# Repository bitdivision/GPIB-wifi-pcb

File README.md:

# GPIB-wifi-pcb
**NOTE**: This is currently not working.
A GPIB adapter using an ESP8266 for wifi functionality and a Cortex M0.

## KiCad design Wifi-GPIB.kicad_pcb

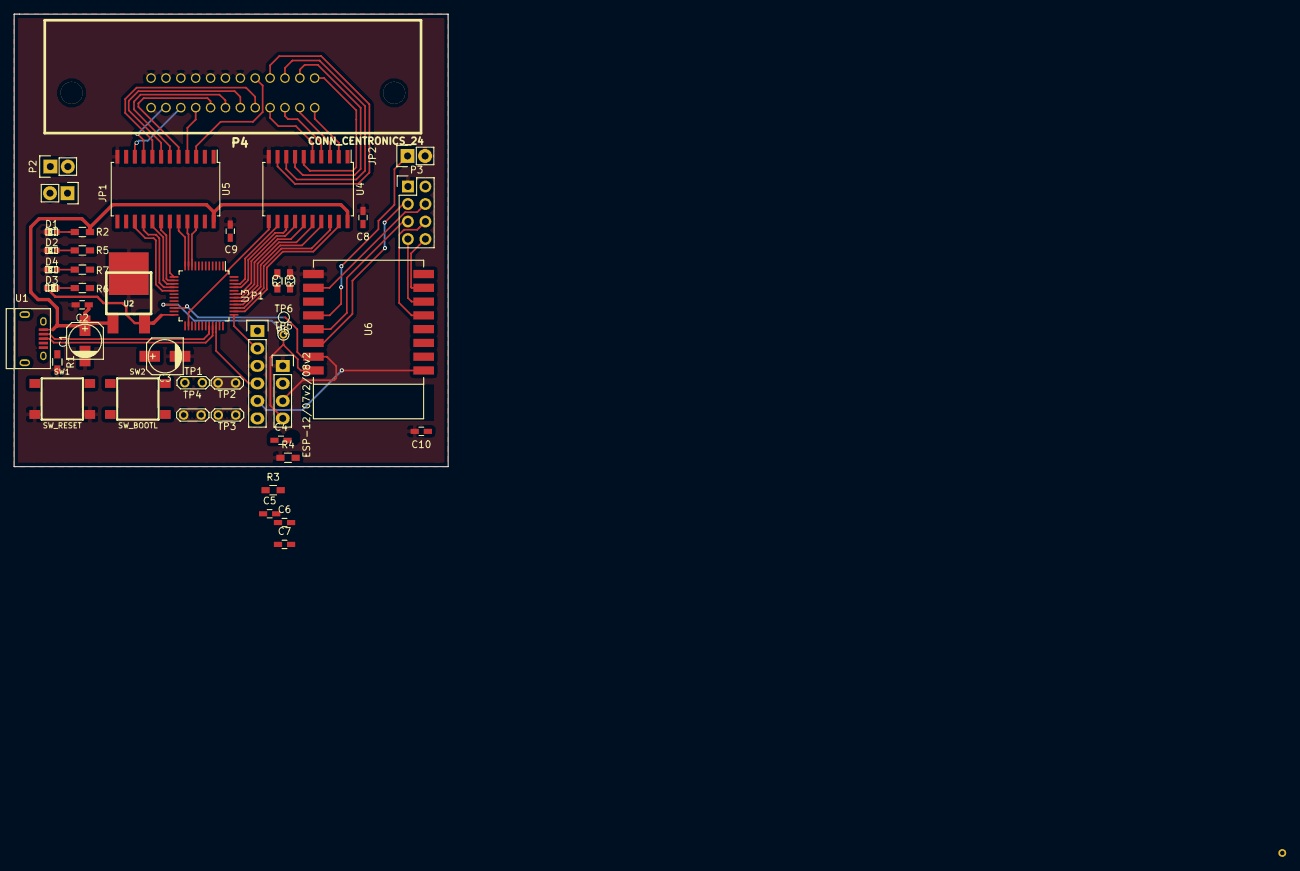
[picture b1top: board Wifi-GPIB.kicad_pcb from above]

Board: 2 copper layers, 63.0 x 65.7 mm, 44 parts (0 on the bottom side), 66 nets.

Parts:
C1, C3: 47u; c_elec_5x5.3
C2: 0.33u; C_0603_HandSoldering
C4, C5, C6, C8, C9: 100n; C_0603_HandSoldering
C7: 1u; C_0603_HandSoldering
C10: C; C_0603_HandSoldering
D1: PWR; LED-0603
D2: WIFI; LED-0603
D3: USB; LED-0603
D4: GPIB; LED-0603
JP1: USB_LED; Pin_Header_Straight_1x02
JP2: ESP_FLASH_JUMP; Pin_Header_Straight_1x02
P1: SWD; Pin_Header_Straight_1x06
P2: USART; Pin_Header_Straight_1x02
P3: ESP_EXPANSION; Pin_Header_Straight_2x04
P4: CONN_CENTRONICS_24; gpib_conn_male
P5: ESP_PROG; Pin_Header_Straight_1x04
R1: 100k; R_0603_HandSoldering
R2: 270; R_0603_HandSoldering
R3, R4, R5, R6, R7, R8, R9: R; R_0603_HandSoldering
SW1: SW_RESET; SW_PUSH_SMD
SW2: SW_BOOTL; SW_PUSH_SMD
TP1, TP2, TP3, TP4: TESTPOINT
TP5, TP6: TESTPOINT; PINTST
U1: MICRO-B_USB; USB_Micro-B
U2: BA33BC0FP-E2; TO-252
U3: STM32F072CBT6; LQFP-48_7x7mm_Pitch0.5mm
U4: SN75160B; SOIC-20_7.5x12.8mm_Pitch1.27mm
U5: SN75162B; SOIC-24_7.5x15.4mm_Pitch1.27mm
U6: ESP-12/07v2/08v2; ESP-07

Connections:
+3.3V: C3.1, C4.2, C6.2, C7.2, C10.1, D3.1, P1.1, P3.2, P5.2, R3.2, R8.1, SW2.2, TP1.1, U2.3, U3.9, U3.24, U3.36, U3.48, U6.3, U6.8, U6.11
+5V: C1.1, C2.1, C8.1, C9.1, R2.1, TP2.1, U1.1, U2.1, U4.20, U5.24
/GPIB and Cortex M0/ATN: U3.16, U5.16
/GPIB and Cortex M0/D1: U3.38, U4.19
/GPIB and Cortex M0/D2: U3.39, U4.18
/GPIB and Cortex M0/D3: U3.40, U4.17
/GPIB and Cortex M0/D4: U3.41, U4.16
/GPIB and Cortex M0/D5: U3.42, U4.15
/GPIB and Cortex M0/D6: U3.43, U4.14
/GPIB and Cortex M0/D7: U3.45, U4.13
/GPIB and Cortex M0/D8: U3.46, U4.12
/GPIB and Cortex M0/DAV: U3.14, U5.18
/GPIB and Cortex M0/EOI: U3.15, U5.17
/GPIB and Cortex M0/ESP_GPIO_4: P3.3, U6.14
/GPIB and Cortex M0/ESP_GPIO_5: P3.5, U6.13
/GPIB and Cortex M0/ESP_GPIO_12: P3.7, U6.6
/GPIB and Cortex M0/ESP_GPIO_13: P3.8, U6.7
/GPIB and Cortex M0/ESP_GPIO_14: P3.6, U6.5
/GPIB and Cortex M0/ESP_GPIO_15: P3.4, R9.1, U6.10
/GPIB and Cortex M0/ESP_GPIO_16: R5.2, U6.4
/GPIB and Cortex M0/ESP_RXD: P5.3, TP6.1, U3.22, U6.15
/GPIB and Cortex M0/ESP_TXD: P5.4, TP5.1, U3.21, U6.16
/GPIB and Cortex M0/IFC: U3.11, U5.21
/GPIB and Cortex M0/NDAC: U3.12, U5.20
/GPIB and Cortex M0/NRFD: U3.13, U5.19
/GPIB and Cortex M0/REN: U3.10, U5.22
/GPIB and Cortex M0/SRQ: U3.17, U5.15
/GPIB and Cortex M0/USB_D+: U1.3, U3.33
/GPIB and Cortex M0/USB_D-: U1.2, U3.32
BOOT0: R4.2, SW2.1, U3.44
ESP_GPIO0: JP2.1, R8.2, U6.12
GND: C1.2, C2.2, C3.2, C5.1, C6.1, C7.1, C8.2, C9.2, C10.2, D1.2, D2.2, D4.2, JP2.2, P1.3, P3.1, P4.12, P4.18, P4.19, P4.20, P4.21, P4.22, P4.23, P4.24, P5.1, R1.2, R4.1, R9.2, SW1.2, TP3.1, TP4.1, U1.5, U2.2, U3.8, U3.23, U3.35, U3.47, U4.10, U5.12, U6.9
GPIB_BUS_ATN: P4.11, U5.9
GPIB_BUS_D1: P4.1, U4.2
GPIB_BUS_D2: P4.2, U4.3
GPIB_BUS_D3: P4.3, U4.4
GPIB_BUS_D4: P4.4, U4.5
GPIB_BUS_D5: P4.13, U4.6
GPIB_BUS_D6: P4.14, U4.7
GPIB_BUS_D7: P4.15, U4.8
GPIB_BUS_D8: P4.16, U4.9
GPIB_BUS_DAV: P4.6, U5.7
GPIB_BUS_EOI: P4.5, U5.8
GPIB_BUS_IFC: P4.9, U5.4
GPIB_BUS_NDAC: P4.8, U5.5
GPIB_BUS_NRFD: P4.7, U5.6
GPIB_BUS_REN: P4.17, U5.3
GPIB_BUS_SRQ: P4.10, U5.10
GPIB_CTRL_DC: U3.18, U5.13
GPIB_CTRL_SC: U3.20, U5.1
GPIB_CTRL_TE: U3.19, U5.2
GPIB_DATA_PE: U3.26, U4.11
GPIB_DATA_TE: U3.25, U4.1
GPIB_SEND_LED: R7.2, U3.28
NRST: C5.2, P1.5, R3.1, SW1.1, U3.7, U6.1
unnamed: C4.1, U3.1
unnamed: D1.1, R2.2
unnamed: D2.1, R5.1
unnamed: D3.2, R6.1
unnamed: D4.1, R7.1
unnamed: R1.1, U1.4
SWCLK: P1.2, U3.37
SWDIO: JP1.1, P1.4, U3.34
USART1_RX: P2.2, U3.31
USART1_TX: P2.1, U3.30
USB_NOE: JP1.2, R6.2

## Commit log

2015-05-26 Added most of components to sch
2015-05-26 Add ESP library
2015-05-26 Add ESP to sch
2015-05-26 Add gitignore
2015-05-26 Add new Voltage Regulator
2015-05-26 Add new voltage regulator to sch
2015-05-26 Add power test points and add ESP programming header
2015-05-26 Add Vin test point
2015-05-26 ESP mostly wired up. Need to decide on M0 -> ESP interface
2015-05-26 Fix some labels
2015-05-27 Started dividing subsheets and sorted out power circuits. Active switching on USB/DC connector 5V.
2015-05-27 Add sheets
2015-05-27 Update main sch to reference heirarchy. Add some more stuff to ESP.
2015-05-27 Add testpoints and tidy up
2015-05-28 More cleanup and swap out M0 model
2015-05-28 Add a few more libs
2015-05-28 Finish USB and test points for power
2015-05-28 Add correct pin names from datasheet for stm32f072. Some lovely vim macros here :)
2015-05-28 Add new stm32f072 to sch
2015-05-28 Connect up USB pins
2015-05-28 Add USB activity LED
2015-05-28 Wired up GPIB bus side
2015-05-28 Fix up GPIB port labels
2015-05-30 Add reset circuit
2015-05-30 initial GPIB pin mappings
2015-05-30 ESP Serial interface
2015-05-30 ESP doesn't seem to support UART2, switch to UART1
    As far as I can tell the TXD2, RXD2 ports are not documented
    If they do work, they will only work exclusively of TX1/RX1.
    So better to just use the main UART.
2015-05-30 Add rst to debug conn
2015-05-30 Use ST-Link (standard?) header
2015-05-31 Think sch finished
2015-05-31 DRCs mostly fixed
2015-05-31 Start routing
2015-06-01 Need to swap gpib line driver buses on stm32
2015-06-01 Remove Barrel Jack and associated power circuits. Unnecessary for now and add a lot of complexity / BOM cost
2015-06-01 Rebuilt annotations and update layout
2015-06-01 Placement pretty much there
2015-06-03 More routing
